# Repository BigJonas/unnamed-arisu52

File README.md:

# What is this ?
This project is a alice style (since it has arrow keys its an arisu) 54 percent keyboard. Layout is most likely final because i don't really feel like changing it.

# Changes I would like to make in another revision
Throughout the design process of making a keyboard i find things that I find that would make things easier or would be cool feature. However it would be difficult to impliment half-way through a project. Here are some of the things i would like to implement

* Duplex matrix, [See here](https://kbd.news/pic/article/1391/keyboard-matrix-japanese-duplex-3x4.png)
    
    Something I saw on ai03's keyboard guide, it seemed interesting and a neat little challenge, also uses less pins and makes routing to the mcu easier while making routing the matrix harder. This would require me to also code a custom algorithm for scanning.

* Internally split keyboard
    
    To have two seperate pcbs mounted on the inside of the keyboard, allowing for a softer typing experience, perhaps a daughter board that connects both boards and is the usb ports.
        
* Flex cuts
    
   Although Im not too confident in the flex cuts being needed some small flex cuts would be nice. This could compliment the stiffness of some stiffer materials I plan to use on the plate

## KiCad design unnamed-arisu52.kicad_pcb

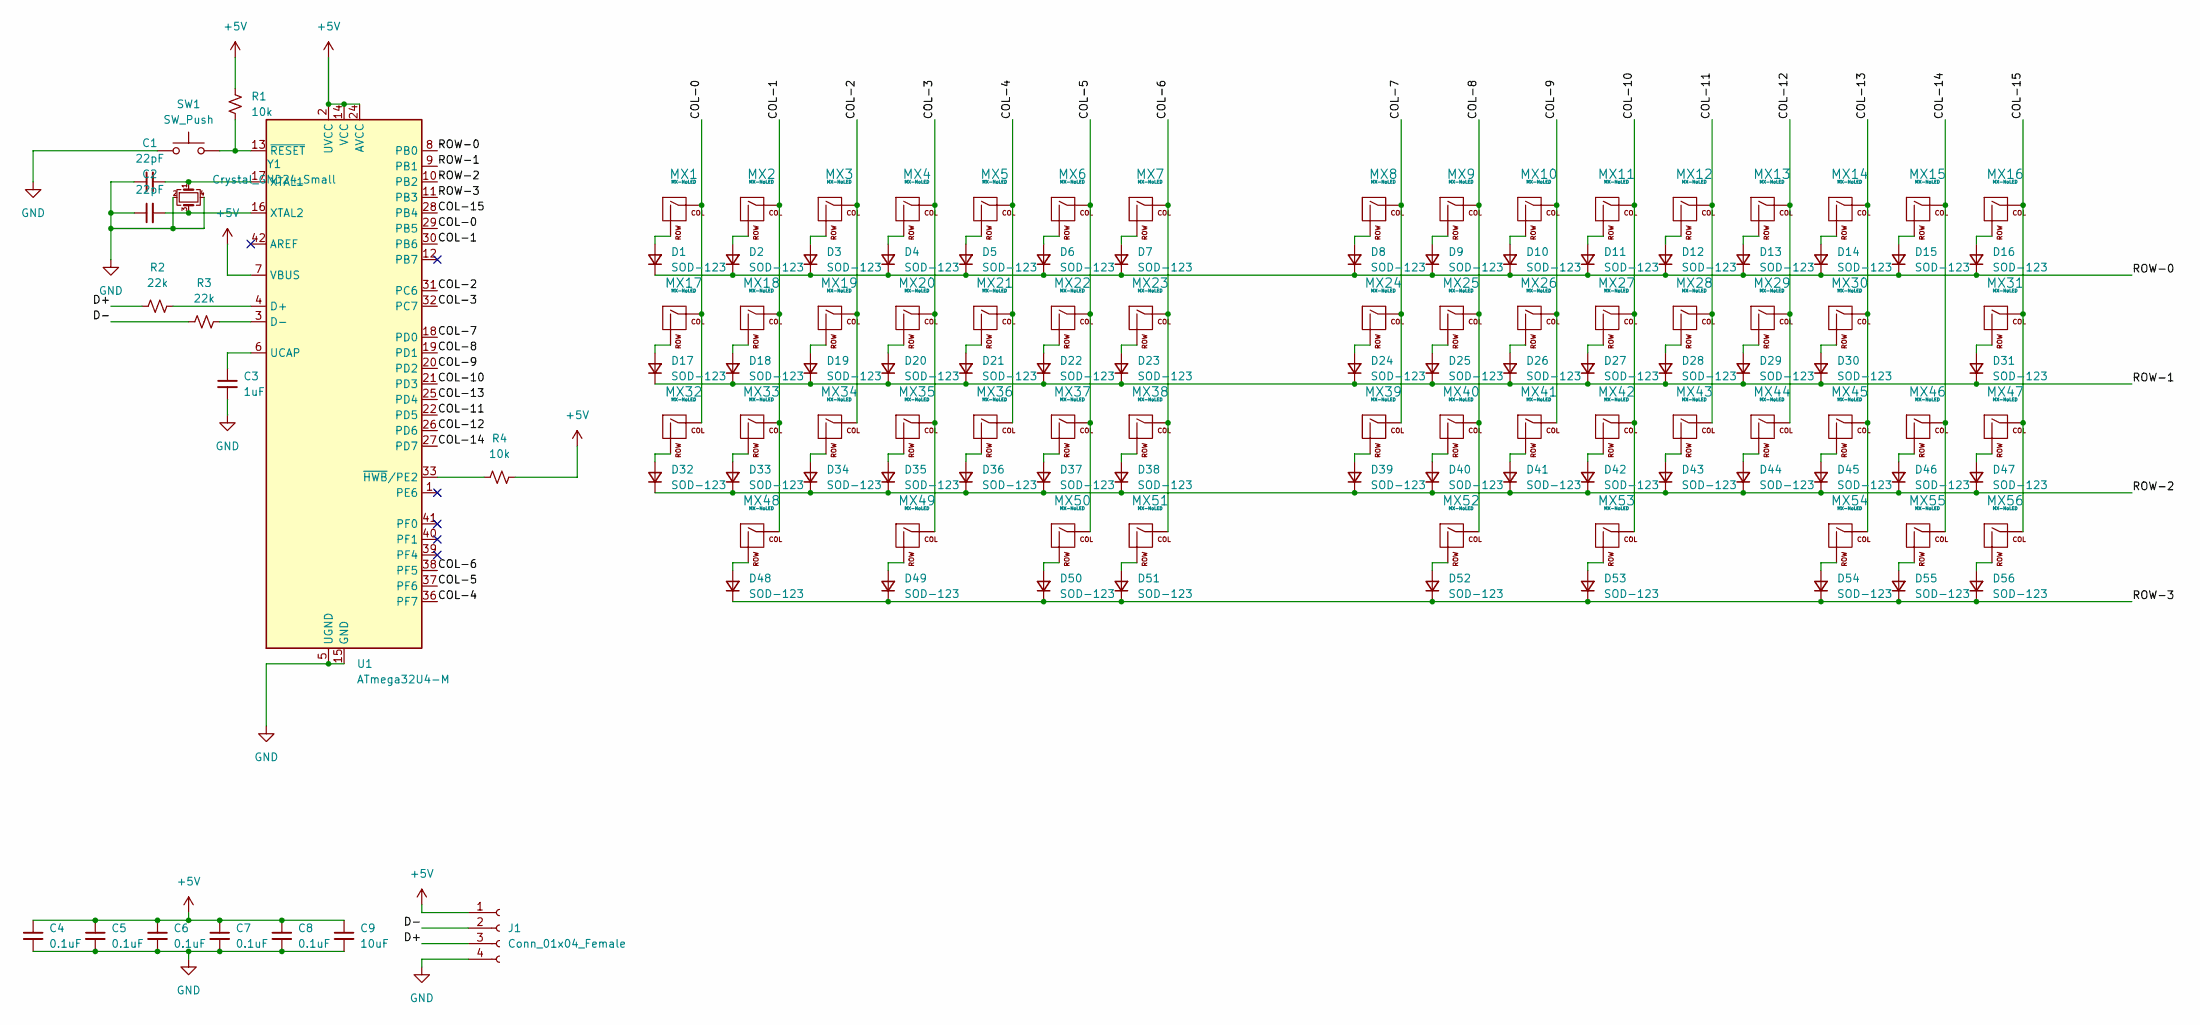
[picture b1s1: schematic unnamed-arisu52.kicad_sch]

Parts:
C1, C2: 22pF; C_0603_1608Metric_Pad1.08x0.95mm_HandSolder
C3: 1uF; C_0603_1608Metric_Pad1.08x0.95mm_HandSolder
C4, C5, C6, C7, C8: 0.1uF; C_0603_1608Metric_Pad1.08x0.95mm_HandSolder
C9: 10uF; C_0603_1608Metric_Pad1.08x0.95mm_HandSolder
D1, D2, D3, D4, D5, D6, D7, D8, D9, D10, D11, D12, D13, D14, D15, D16, D17, D18, D19, D20, D21, D22, D23, D24, D25, D26, D27, D28, D29, D30, D31, D32, D33, D34, D35, D36, D37, D38, D39, D40, D41, D42, D43, D44, D45, D46, D47, D48, D49, D50, D51, D52, D53, D54, D55, D56: SOD-123; D_SOD-123
J1: Conn_01x04_Female; SM04B-SRSS-TB(LF)(SN)
MX1, MX3, MX4, MX5, MX6, MX7, MX8, MX9, MX10, MX11, MX12, MX13, MX14, MX16, MX17, MX19, MX20, MX21, MX22, MX23, MX24, MX25, MX26, MX27, MX28, MX29, MX31, MX32, MX34, MX35, MX36, MX37, MX38, MX39, MX40, MX41, MX42, MX43, MX44, MX46, MX47, MX51, MX54, MX55, MX56: MX-NoLED; MXOnly-1U-NoLED
MX2, MX15, MX48, MX49, MX53: MX-NoLED; MXOnly-1.5U-NoLED
MX18: MX-NoLED; MXOnly-1.25U-NoLED
MX30, MX50: MX-NoLED; MXOnly-2.25U-ReversedStabilizers-NoLED
MX33: MX-NoLED; MXOnly-2.25U-NoLED
MX45: MX-NoLED; MXOnly-1.75U-NoLED
MX52: MX-NoLED; MXOnly-2.75U-ReversedStabilizers-NoLED
R1, R4: 10k; R_0603_1608Metric_Pad0.98x0.95mm_HandSolder
R2, R3: 22k; R_0603_1608Metric_Pad0.98x0.95mm_HandSolder
SW1: SW_Push; SKQG-1155865
U1: ATmega32U4-M; QFN-44-1EP_7x7mm_P0.5mm_EP5.2x5.2mm
Y1: Crystal_GND24_Small; Crystal_SMD_3225-4Pin_3.2x2.5mm_HandSoldering

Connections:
+5V: C4.1, C5.1, C6.1, C7.1, C8.1, C9.1, J1.1, R1.1, R4.1, U1.2 (UVCC), U1.7 (VBUS), U1.14 (VCC), U1.24 (AVCC), U1.34 (VCC), U1.44 (AVCC)
/COL-0: MX1.1 (COL), MX17.1 (COL), MX32.1 (COL), U1.29 (PB5)
/COL-1: MX2.1 (COL), MX18.1 (COL), MX33.1 (COL), MX48.1 (COL), U1.30 (PB6)
/COL-2: MX3.1 (COL), MX19.1 (COL), MX34.1 (COL), U1.31 (PC6)
/COL-3: MX4.1 (COL), MX20.1 (COL), MX35.1 (COL), MX49.1 (COL), U1.32 (PC7)
/COL-4: MX5.1 (COL), MX21.1 (COL), MX36.1 (COL), U1.36 (PF7)
/COL-5: MX6.1 (COL), MX22.1 (COL), MX37.1 (COL), MX50.1 (COL), U1.37 (PF6)
/COL-6: MX7.1 (COL), MX23.1 (COL), MX38.1 (COL), MX51.1 (COL), U1.38 (PF5)
/COL-7: MX8.1 (COL), MX24.1 (COL), MX39.1 (COL), U1.18 (PD0)
/COL-8: MX9.1 (COL), MX25.1 (COL), MX40.1 (COL), MX52.1 (COL), U1.19 (PD1)
/COL-9: MX10.1 (COL), MX26.1 (COL), MX41.1 (COL), U1.20 (PD2)
/COL-10: MX11.1 (COL), MX27.1 (COL), MX42.1 (COL), MX53.1 (COL), U1.21 (PD3)
/COL-11: MX12.1 (COL), MX28.1 (COL), MX43.1 (COL), U1.22 (PD5)
/COL-12: MX13.1 (COL), MX29.1 (COL), MX44.1 (COL), U1.26 (PD6)
/COL-13: MX14.1 (COL), MX30.1 (COL), MX45.1 (COL), MX54.1 (COL), U1.25 (PD4)
/COL-14: MX15.1 (COL), MX46.1 (COL), MX55.1 (COL), U1.27 (PD7)
/COL-15: MX16.1 (COL), MX31.1 (COL), MX47.1 (COL), MX56.1 (COL), U1.28 (PB4)
/D+: J1.3, R2.1
/D-: J1.2, R3.1
/ROW-0: D1.1 (K), D2.1 (K), D3.1 (K), D4.1 (K), D5.1 (K), D6.1 (K), D7.1 (K), D8.1 (K), D9.1 (K), D10.1 (K), D11.1 (K), D12.1 (K), D13.1 (K), D14.1 (K), D15.1 (K), D16.1 (K), U1.8 (PB0)
/ROW-1: D17.1 (K), D18.1 (K), D19.1 (K), D20.1 (K), D21.1 (K), D22.1 (K), D23.1 (K), D24.1 (K), D25.1 (K), D26.1 (K), D27.1 (K), D28.1 (K), D29.1 (K), D30.1 (K), D31.1 (K), U1.9 (PB1)
/ROW-2: D32.1 (K), D33.1 (K), D34.1 (K), D35.1 (K), D36.1 (K), D37.1 (K), D38.1 (K), D39.1 (K), D40.1 (K), D41.1 (K), D42.1 (K), D43.1 (K), D44.1 (K), D45.1 (K), D46.1 (K), D47.1 (K), U1.10 (PB2)
/ROW-3: D48.1 (K), D49.1 (K), D50.1 (K), D51.1 (K), D52.1 (K), D53.1 (K), D54.1 (K), D55.1 (K), D56.1 (K), U1.11 (PB3)
GND: C1.1, C2.1, C3.2, C4.2, C5.2, C6.2, C7.2, C8.2, C9.2, J1.4, SW1.1, U1.5 (UGND), U1.15 (GND), U1.23 (GND), U1.35 (GND), U1.43 (GND), U1.45 (GND), Y1.2, Y1.4
unnamed: C1.2, U1.17 (XTAL1), Y1.1
unnamed: C2.2, U1.16 (XTAL2), Y1.3
unnamed: C3.1, U1.6 (UCAP)
unnamed: D1.2 (A), MX1.2 (ROW)
unnamed: D2.2 (A), MX2.2 (ROW)
unnamed: D3.2 (A), MX3.2 (ROW)
unnamed: D4.2 (A), MX4.2 (ROW)
unnamed: D5.2 (A), MX5.2 (ROW)
unnamed: D6.2 (A), MX6.2 (ROW)
unnamed: D7.2 (A), MX7.2 (ROW)
unnamed: D8.2 (A), MX8.2 (ROW)
unnamed: D9.2 (A), MX9.2 (ROW)
unnamed: D10.2 (A), MX10.2 (ROW)
unnamed: D11.2 (A), MX11.2 (ROW)
unnamed: D12.2 (A), MX12.2 (ROW)
unnamed: D13.2 (A), MX13.2 (ROW)
unnamed: D14.2 (A), MX14.2 (ROW)
unnamed: D15.2 (A), MX15.2 (ROW)
unnamed: D16.2 (A), MX16.2 (ROW)
unnamed: D17.2 (A), MX17.2 (ROW)
unnamed: D18.2 (A), MX18.2 (ROW)
unnamed: D19.2 (A), MX19.2 (ROW)
unnamed: D20.2 (A), MX20.2 (ROW)
unnamed: D21.2 (A), MX21.2 (ROW)
unnamed: D22.2 (A), MX22.2 (ROW)
unnamed: D23.2 (A), MX23.2 (ROW)
unnamed: D24.2 (A), MX24.2 (ROW)
unnamed: D25.2 (A), MX25.2 (ROW)
unnamed: D26.2 (A), MX26.2 (ROW)
unnamed: D27.2 (A), MX27.2 (ROW)
unnamed: D28.2 (A), MX28.2 (ROW)
unnamed: D29.2 (A), MX29.2 (ROW)
unnamed: D30.2 (A), MX30.2 (ROW)
unnamed: D31.2 (A), MX31.2 (ROW)
unnamed: D32.2 (A), MX32.2 (ROW)
unnamed: D33.2 (A), MX33.2 (ROW)
unnamed: D34.2 (A), MX34.2 (ROW)
unnamed: D35.2 (A), MX35.2 (ROW)
unnamed: D36.2 (A), MX36.2 (ROW)
unnamed: D37.2 (A), MX37.2 (ROW)
unnamed: D38.2 (A), MX38.2 (ROW)
unnamed: D39.2 (A), MX39.2 (ROW)
unnamed: D40.2 (A), MX40.2 (ROW)
unnamed: D41.2 (A), MX41.2 (ROW)
unnamed: D42.2 (A), MX42.2 (ROW)
unnamed: D43.2 (A), MX43.2 (ROW)
unnamed: D44.2 (A), MX44.2 (ROW)
unnamed: D45.2 (A), MX45.2 (ROW)
unnamed: D46.2 (A), MX46.2 (ROW)
unnamed: D47.2 (A), MX47.2 (ROW)
unnamed: D48.2 (A), MX48.2 (ROW)
unnamed: D49.2 (A), MX49.2 (ROW)
unnamed: D50.2 (A), MX50.2 (ROW)
unnamed: D51.2 (A), MX51.2 (ROW)
unnamed: D52.2 (A), MX52.2 (ROW)
unnamed: D53.2 (A), MX53.2 (ROW)
unnamed: D54.2 (A), MX54.2 (ROW)
unnamed: D55.2 (A), MX55.2 (ROW)
unnamed: D56.2 (A), MX56.2 (ROW)
unnamed: R1.2, SW1.2, U1.13 (~RESET)
unnamed: R2.2, U1.4 (D+)
unnamed: R3.2, U1.3 (D-)
unnamed: R4.2, U1.33 (~HWB/PE2)

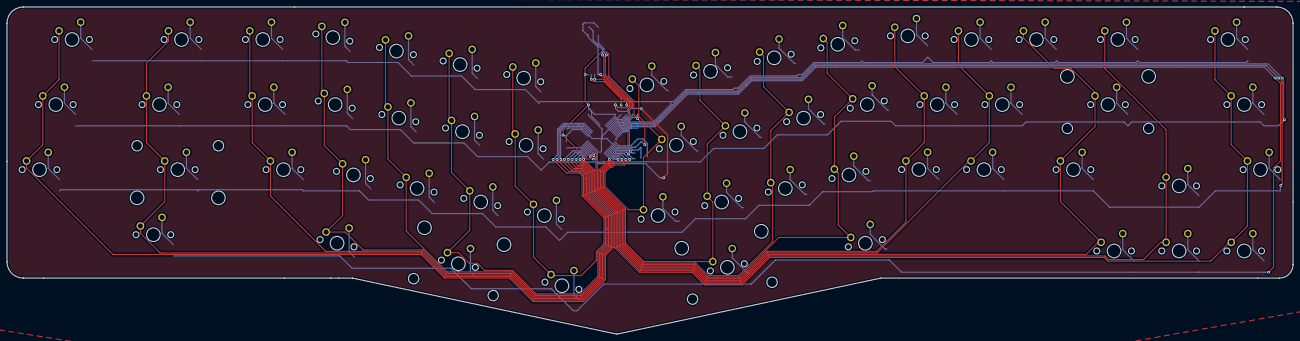
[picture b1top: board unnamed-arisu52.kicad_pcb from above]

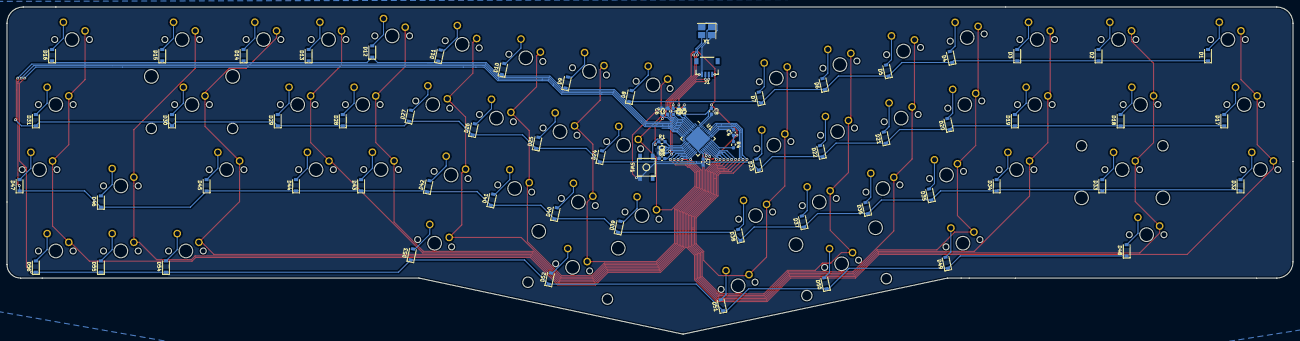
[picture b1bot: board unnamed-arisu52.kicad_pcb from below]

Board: 2 copper layers, 376.6 x 95.8 mm, 129 parts (73 on the bottom side), 87 nets.

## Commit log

2022-11-12 init commit
2022-11-12 added schematic and footprint libraries
2022-11-12 fixed issues relating to kicads default library and project libraries
2022-11-12 laid out electronics schematic, no footprints assigned
2022-11-12 assigned footprints
2022-11-12 resolved some issues with the matrix schematic and laid out the matrix and edge cuts on the pcb
2022-11-12 laid out diodes with respect to the switches
2022-11-12 routed the matrix
2022-11-12 resolved an issue where the jst connector did not have a 3d model
2022-11-12 Added README and included reference for pcb layout
2022-11-13 started laying out electronics
2022-11-13 finished wiring electonics, just need to wire matrix
2022-11-13 routed pins to matrix and resolved some drc issues
2022-11-13 added ground fills, note: so jankey in kicad 6
2022-11-13 bro i dont know what this commit is maybe the last commit
2022-11-13 Used wrong link in README.md
